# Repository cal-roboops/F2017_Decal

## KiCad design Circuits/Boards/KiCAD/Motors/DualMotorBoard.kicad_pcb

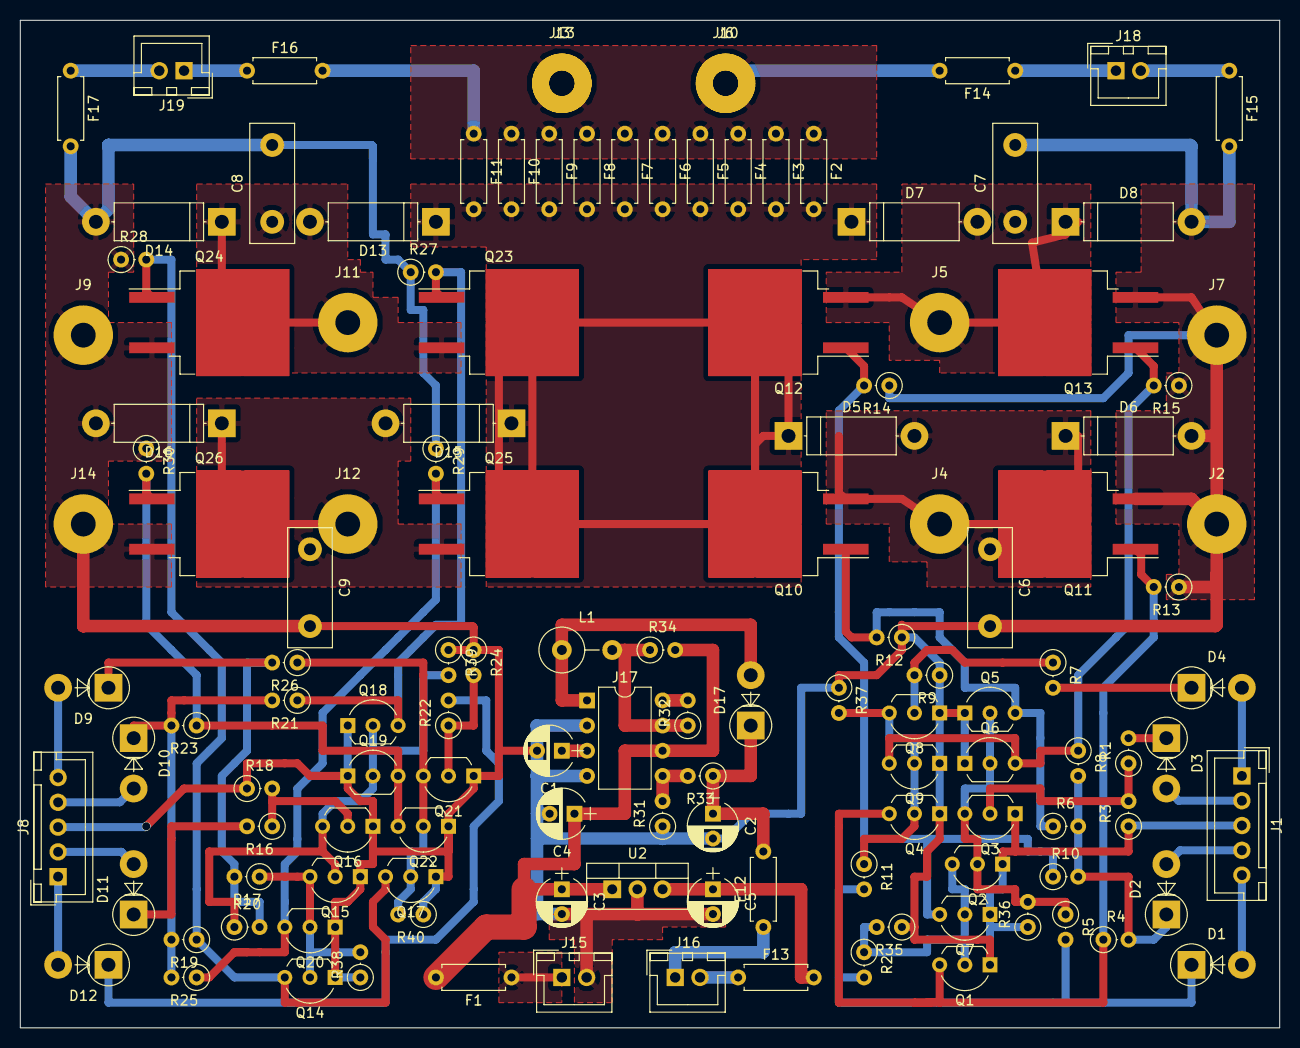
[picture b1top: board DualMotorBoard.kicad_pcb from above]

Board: 2 copper layers, 127.0 x 101.6 mm, 130 parts (0 on the bottom side), 56 nets.

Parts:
C1: 470pF; CP_Radial_D5.0mm_P2.50mm
C2: 470uF; CP_Radial_D5.0mm_P2.50mm
C3: 100uF; CP_Radial_D5.0mm_P2.50mm
C4: 0.33uF; CP_Radial_D5.0mm_P2.50mm
C5: 0.1uF; CP_Radial_D5.0mm_P2.50mm
C6, C7, C8, C9: 1200uF; C_Disc_D12.0mm_W4.4mm_P7.75mm
D1, D2, D3, D4, D9, D10, D11, D12, D17: 1N4007; D_5W_P5.08mm_Vertical_AnodeUp
D5, D6, D7, D8, D13, D14, D15, D16: 1N4007; D_5W_P12.70mm_Horizontal
F1, F2, F3, F4, F5, F6, F7, F8, F9, F10, F11, F12, F13, F14, F15, F16, F17: Polyfuse; R_Axial_DIN0207_L6.3mm_D2.5mm_P7.62mm_Horizontal
J1, J8: Conn_01x05; JST_XH_B05B-XH-A_05x2.50mm_Straight
J2, J3, J4, J5, J6, J7, J9, J10, J11, J12, J13, J14: Conn_01x01; SolderWirePad_single_2-5mmDrill
J15, J16, J18, J19: Conn_01x02; JST_XH_B02B-XH-A_02x2.50mm_Straight
J17: MC34063; DIP-8_W7.62mm
L1: 150uH; L_Axial_L11.0mm_D4.5mm_P5.08mm_Vertical_Fastron_MECC
Q1, Q2, Q3, Q4, Q5, Q6, Q7, Q8, Q9, Q14, Q15, Q16, Q17, Q18, Q19, Q20, Q21, Q22: 2N3904; TO-92_Inline_Wide
Q10, Q11, Q12, Q13, Q23, Q24, Q25, Q26: Q_NMOS_DGS; TO-263-2
R1, R3, R4, R6, R7, R8, R9, R10, R13, R15, R16, R18, R19, R21, R22, R23, R24, R25, R28, R30, R35, R36, R37, R38, R39, R40: 10K; R_Axial_DIN0207_L6.3mm_D2.5mm_P2.54mm_Vertical
R2, R5, R11, R17, R20, R26, R31, R32: 1K; R_Axial_DIN0207_L6.3mm_D2.5mm_P2.54mm_Vertical
R12, R14, R27, R29: 1Meg; R_Axial_DIN0207_L6.3mm_D2.5mm_P2.54mm_Vertical
R33: 20K; R_Axial_DIN0207_L6.3mm_D2.5mm_P2.54mm_Vertical
R34: 0.22; R_Axial_DIN0207_L6.3mm_D2.5mm_P2.54mm_Vertical
U2: LM7805_TO220; TO-220-3_Vertical

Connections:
+BATT: F2.1, F3.1, F4.1, F5.1, F6.1, F7.1, F8.1, F9.1, F10.1, F11.1, F14.2, F16.2, J3.1, J6.1, J10.1, J13.1
/5VUnit/VOUT: C5.1, F13.2, U2.3
/26VUnit/N$5: D17.2, J17.1, L1.1
/26VUnit/N$10: C1.1, J17.3
/26VUnit/N$12: J17.7, L1.2, R32.1, R34.1
/26VUnit/N$13: J17.5, R31.2, R33.2
/26VUnit/VIN: C3.1, C4.1, F1.2, J17.6, R34.2, U2.1
/26VUnit/VOUT: C2.1, D17.1, F12.2, R33.1
/MotorControlUnit_1/BBM: Q1.3, Q4.3, Q11.1, R4.1, R13.2
/MotorControlUnit_1/DVG: D2.1, R4.2, R6.2, R8.2, R10.2
/MotorControlUnit_1/DVSW: D1.1, R2.2, R5.2, R11.2
/MotorControlUnit_1/Dir: D3.1, R1.2
/MotorControlUnit_1/DirSel: Q3.2, R1.1, R3.2
/MotorControlUnit_1/FBM: Q6.3, Q9.3, Q13.1, R8.1, R15.2
/MotorControlUnit_1/MBB: Q1.2, Q2.3, Q7.2, R2.1, R35.2
/MotorControlUnit_1/MBF: Q7.3, Q12.1, R10.1, R14.2
/MotorControlUnit_1/MFB: Q2.2, Q3.3, Q5.2, Q6.2, R5.1, R36.2
/MotorControlUnit_1/MFF: Q5.3, Q10.1, R6.1, R12.2
/MotorControlUnit_1/Speed: D4.1, R7.2
/MotorControlUnit_1/SpeedSel: Q8.2, R7.1, R9.2
/MotorControlUnit_1/VB: C7.1, D7.2, D8.1, J5.1, Q12.3, Q13.2
/MotorControlUnit_1/VF: C6.1, D5.2, D6.1, J4.1, Q10.3, Q11.2
/MotorControlUnit_1/VFUSE: D5.1, D7.1, D13.1, D15.1, F2.2, F3.2, F4.2, F5.2, F6.2, F7.2, F8.2, F9.2, F10.2, F11.2, Q10.2, Q12.2, Q23.2, Q25.2
/MotorControlUnit_1/VG: D2.2, J1.4
/MotorControlUnit_1/VSW: D1.2, J1.5
/MotorControlUnit_1/iSpeed: Q4.2, Q8.3, Q9.2, R11.1, R37.2
/MotorControlUnit_2/BBM: Q14.3, Q17.3, Q24.1, R19.1, R28.2
/MotorControlUnit_2/DVG: D10.1, R19.2, R21.2, R23.2, R25.2
/MotorControlUnit_2/DVSW: D9.1, R17.2, R20.2, R26.2
/MotorControlUnit_2/Dir: D11.1, R16.2
/MotorControlUnit_2/DirSel: Q16.2, R16.1, R18.2
/MotorControlUnit_2/FBM: Q19.3, Q22.3, Q26.1, R23.1, R30.2
/MotorControlUnit_2/MBB: Q14.2, Q15.3, Q20.2, R17.1, R38.2
/MotorControlUnit_2/MBF: Q20.3, Q25.1, R25.1, R29.2
/MotorControlUnit_2/MFB: Q15.2, Q16.3, Q18.2, Q19.2, R20.1, R39.2
/MotorControlUnit_2/MFF: Q18.3, Q23.1, R21.1, R27.2
/MotorControlUnit_2/Speed: D12.1, R22.2
/MotorControlUnit_2/SpeedSel: Q21.2, R22.1, R24.2
/MotorControlUnit_2/VB: C9.1, D15.2, D16.1, J12.1, Q25.3, Q26.2
/MotorControlUnit_2/VF: C8.1, D13.2, D14.1, J11.1, Q23.3, Q24.2
/MotorControlUnit_2/VG: D10.2, J8.4
/MotorControlUnit_2/VSW: D9.2, J8.5
/MotorControlUnit_2/iSpeed: Q17.2, Q21.3, Q22.2, R26.1, R40.2
GND: C1.2, C2.2, C3.2, C4.2, C5.2, C6.2, C7.2, C8.2, C9.2, D6.2, D8.2, D14.2, D16.2, F15.2, F17.2, J1.3, J2.1, J7.1, J8.3, J9.1, J14.1, J15.2, J17.2, J17.4, Q1.1, Q2.1, Q3.1, Q4.1, Q5.1, Q6.1, Q7.1, Q8.1, Q9.1, Q11.3, Q13.3, Q14.1, Q15.1, Q16.1, Q17.1, Q18.1, Q19.1, Q20.1, Q21.1, Q22.1, Q24.3, Q26.3, R3.1, R9.1, R12.1, R13.1, R14.1, R15.1, R18.1, R24.1, R27.1, R28.1, R29.1, R30.1, R31.1, R35.1, R36.1, R37.1, R38.1, R39.1, R40.1, U2.2
unnamed: D3.2, J1.2
unnamed: D4.2, J1.1
unnamed: D11.2, J8.2
unnamed: D12.2, J8.1
unnamed: F1.1, J15.1
unnamed: F12.1, J16.1
unnamed: F13.1, J16.2
unnamed: F14.1, J18.1
unnamed: F15.1, J18.2
unnamed: F16.1, J19.1
unnamed: F17.1, J19.2
unnamed: J17.8, R32.2

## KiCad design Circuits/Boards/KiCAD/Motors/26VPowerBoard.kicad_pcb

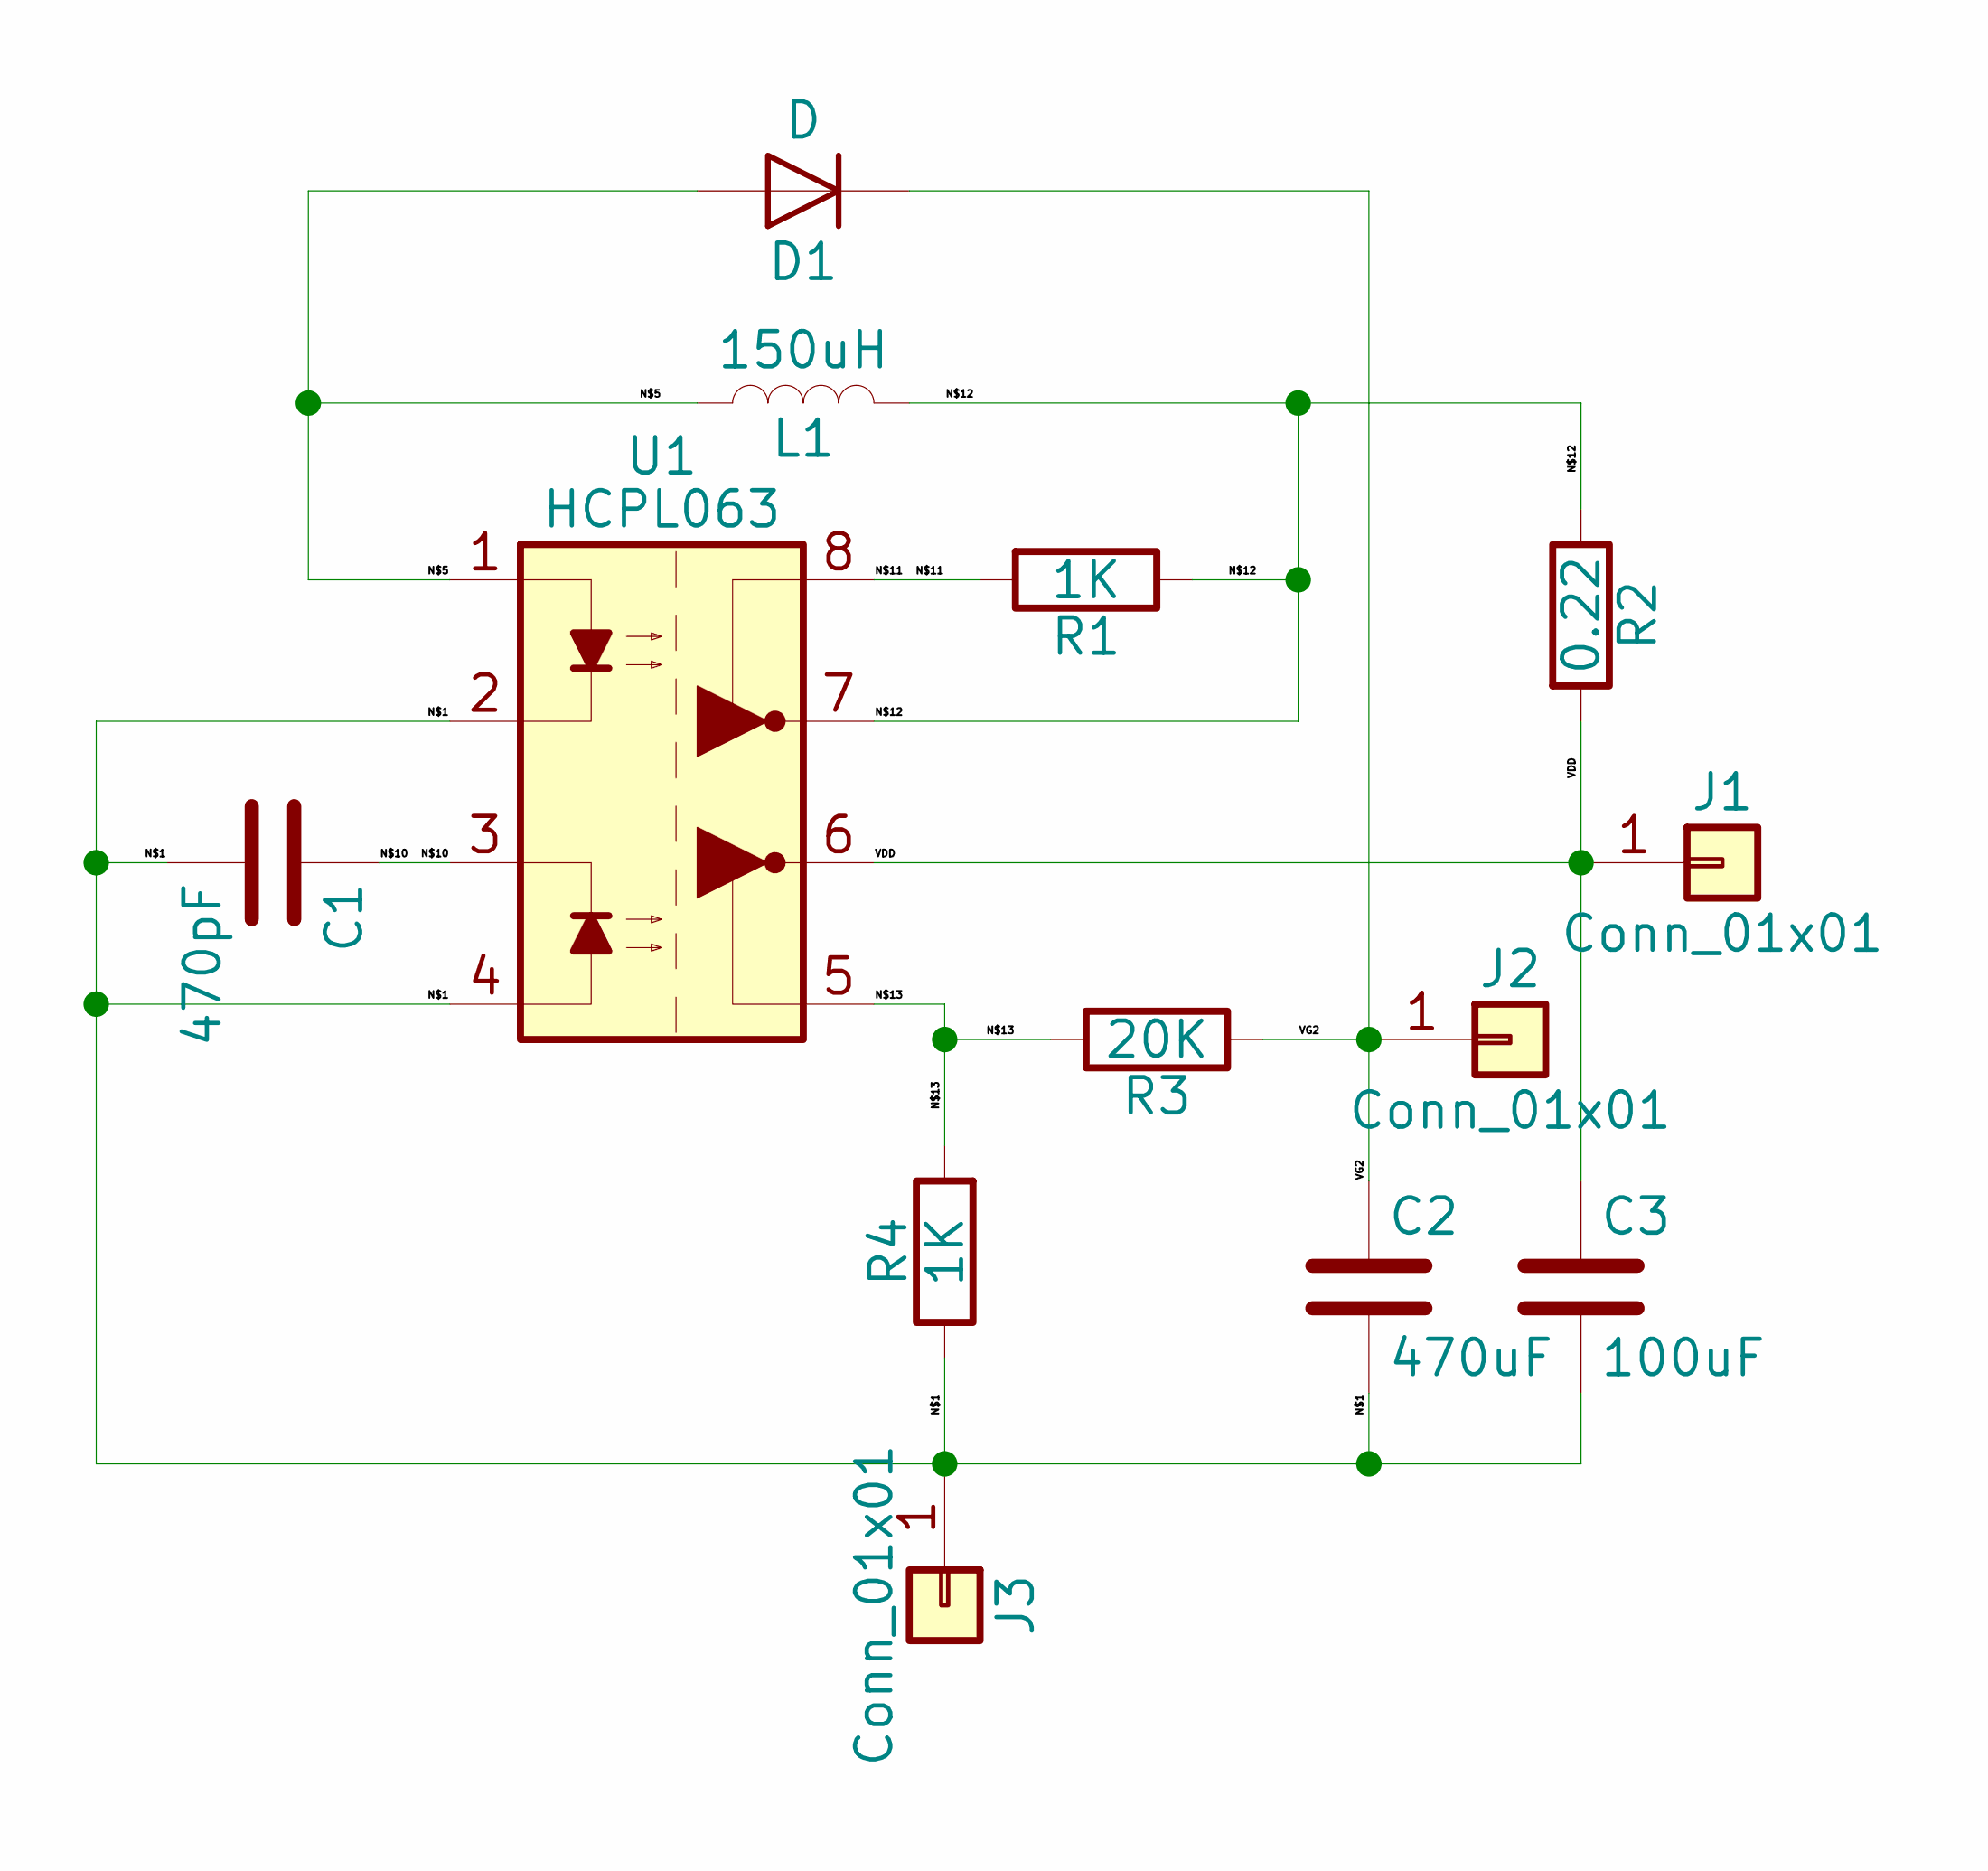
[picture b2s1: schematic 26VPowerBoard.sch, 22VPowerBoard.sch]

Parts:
C1: 470pF; CP_Radial_D5.0mm_P2.50mm
C2: 470uF; CP_Radial_D5.0mm_P2.50mm
C3: 100uF; CP_Radial_D5.0mm_P2.50mm
D1: D; D_5W_P5.08mm_Vertical_AnodeUp
J1, J2: Conn_01x01; MountingHole_2.7mm_Pad_Via
J3: Conn_01x01
L1: 150uH; L_Axial_L11.0mm_D4.5mm_P5.08mm_Vertical_Fastron_MECC
R1, R4: 1K; R_Axial_DIN0207_L6.3mm_D2.5mm_P2.54mm_Vertical
R2: 0.22; R_Axial_DIN0207_L6.3mm_D2.5mm_P2.54mm_Vertical
R3: 20K; R_Axial_DIN0207_L6.3mm_D2.5mm_P2.54mm_Vertical
U1: HCPL063; DIP-8_W7.62mm

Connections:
/N$1: C1.2, C2.2, C3.2, J3.1, R4.1, U1.2 (C1), U1.4 (C2)
/N$5: D1.2 (A), L1.1, U1.1 (A1)
/N$10: C1.1, U1.3 (A2)
/N$11: R1.2, U1.8 (VCC)
/N$12: L1.2, R1.1, R2.1, U1.7 (VO1)
/N$13: R3.2, R4.2, U1.5 (GND)
/VDD: C3.1, J1.1, R2.2, U1.6 (VO2)
/VG2: C2.1, D1.1 (K), J2.1, R3.1

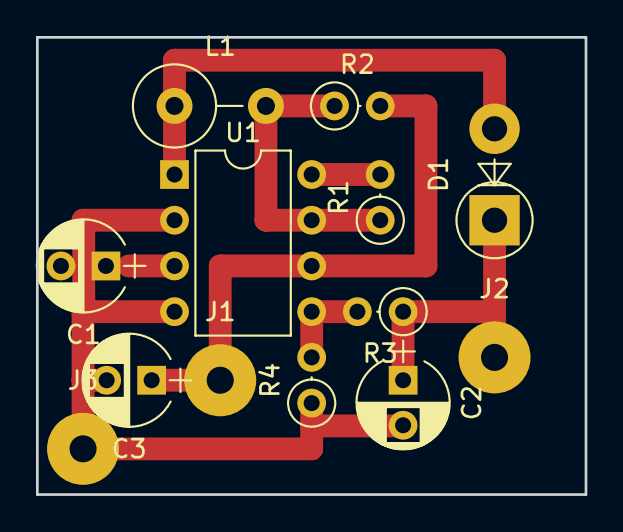
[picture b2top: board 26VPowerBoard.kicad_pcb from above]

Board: 2 copper layers, 30.5 x 25.4 mm, 13 parts (0 on the bottom side), 8 nets.

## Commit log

2017-08-22 Project creation and gitignore added
2017-08-23 added button that prints to debud
2017-08-23 added text box + submit data button for text box
2017-08-24 made client server with text boxes
2017-08-24 Organization and fine tuning of messenger demo
2017-08-28 local webcam button working
2017-09-18 Added backend server, with basic client, and GUI test client
2017-09-18 Updated gitignore and removed qt exe's
2017-09-21 Added Circuit sims
2017-09-21 Making motor controller feedback loop
2017-09-21 Updated Op-Amp in Logic:
2017-09-25 Updated motor simulation
2017-09-25 Ignore simulation raw files
2017-09-26 Save point before PNP control implementation
2017-09-26 Working motor controller simulation
2017-09-27 Small changes
2017-09-27 Pathing Upload
2017-09-28 Split up motor simulation and defiend high pwoer line
2017-09-30 Updated client/server and made changes to motor controller
2017-10-01 server.cpp V4
2017-10-05 Motor controller updates
2017-10-05 Updated motor controller
2017-10-08 Updated server script and vlc multicast
2017-10-08 Updated proxy client and server classes
2017-10-08 ass1
2017-10-08 Setting up rover client
2017-10-15 deleted Circuits, Pathing, and QtMessengerDemo folders
2017-10-15 Simplified motor controller circuit and added FPGA implmentation specifications
2017-10-16 Updated regulator circuits
2017-10-17 json communication/mutexes/function structs
2017-10-17 server now communicates to rover and back to clients
2017-10-18 updated files
2017-10-18 Added custom motor controller tester
2017-10-25 update all clients
2017-10-25 miscellaneous change
2017-10-25 adding assignment3 code - edward
2017-10-25 git example change
2017-10-25 basic impl of topological pathing done
2017-10-26 cleaned up topological pathing code
2017-10-27 changed path drawing
2017-10-27 made window with buttons that change pages
2017-10-27 added regular controls panel
2017-11-01 Fixed motor controller test code - works as expected now
2017-11-01 tank page
2017-11-01 tank done -- can't move to qtproxy yet
2017-11-03 move control_GUI code to QtProxyClient and two ui windows working
2017-11-03 tank done
2017-11-04 Motor control code updated
2017-11-04 Updated gitigore and removed build-Qt dirs
2017-11-06 Updated encoder reading and motor controller
2017-11-08 updated server/client files; added json.hpp
2017-11-08 removed unnecessary line in server.cpp
2017-11-08 added various python scripts for static image processing
2017-11-08 Removed assignment zip
2017-11-08 fixed buffer reset bug
2017-11-10 bug fix to calc_drops function in pathing
2017-11-10 using variance to calc drops
2017-11-10 finished assignemnt 4 and 5
2017-11-10 finished assignment 4 & 5
    :
    "
2017-11-10 implemented slider label
2017-11-11 Updated SSI for encoder and added programmer
2017-11-11 Cleaned up code in programmer to facilitate bug hunt
2017-11-12 updated client.cpp, server.cpp
2017-11-15 added berkeley map
2017-11-15 fixed typo
2017-11-15 Working on programmer and electronics layout
2017-11-17 added 3 buttons to enable/disable buttons (part 1 of assignment 6)
2017-11-17 implemented new buttons to enable/disable control panel
2017-11-17 implemented buttons
2017-11-17 implememnted control buttons
2017-11-21 updated server.cpp
2017-11-29 fix radio button
2017-11-29 cleaned up pathing script and optimized astar
2017-11-29 control panel with serving working. still need to rename files
2017-11-29 one of the json values was wrong
2017-11-30 fixed access control bug
2017-11-30 fixed key press bug
2017-12-01 fixed some more bugs and styled gui more
2017-12-01 more minor style updates
2017-12-01 first attempt at risk function for a pointcloud
2017-12-01 added comments
2017-12-08 small edit
2017-12-21 Adding PCB motor controller board layout
2017-12-21 Fixed gitignore for eagle files
2017-12-22 Finished board files and updated gitignore
2017-12-22 Fixed board CNC errors, ready for cutting on othermill
2017-12-24 Minor updates to Motor Controller
2017-12-24 Updated 22V circuit for bought parts
2017-12-26 Split off 22V & 5V circuits, shrunk motor controller and began adding second to single board
2017-12-27 Single board, two motor update
2017-12-27 Ported Motor Controller to DesignSpark and generated Gerber files for Othermill
2017-12-28 Started moving from EAGLE to KiCAD
2017-12-30 Update KiCAD motor controller and Version 2 simulation
2017-12-31 Fixed KiCAD motor controller
2018-01-05 Rerouted motor controller for smaller size
2018-01-06 Adjusted PCB design
2018-01-07 Created subcircuit for motor control and routing dual controller
2018-01-07 Finished routing dual motor controller, needs to be cleaned up
2018-01-07 Added 26V and 5V units to the Dual motor controller board
2018-01-07 Fixed missing connections and routing
2018-01-07 Added drain resistors to gates
2018-01-16 Fixed gitignore to allow KiCAD pro files
2018-01-16 Motor HF adjustments (gate drain resistors)
2018-01-16 Finished rerouting board with new resistors and caps
2018-01-16 Updated layout errors
2018-01-17 Motor board circuit updated after prototype cut
2018-01-18 Fixed missing connections and routing errors
2018-01-18 Added pin outputs for battery to ground (for external connections)
2018-01-18 Transferred all JXT connections to bottomw traces
2018-01-24 Added Basic Xilinx Echo program for Arty Z7
2018-01-24 Updated echo to test FPGA functionality in addition to ethernet echo
2018-01-26 Fixed synthesis errors in vivado
2018-01-26 Updated gitignores for Xilinx suite
2018-01-27 Started rover client for FPGA
2018-02-08 setup arm stuff, added a widget for controlling camera mask but it has no functionality yet
2018-02-08 setup example code for how to do the arm in main.cpp
2018-02-08 minor variable names changes
2018-02-14 minor changes
2018-02-14 added release file
2018-02-16 Added NRF24L01+ base files and code
2018-02-17 Moved and updated files
2018-02-20 added some more functionality for drawer
2018-02-24 Added testing for nRF24 module
2018-02-24 FPGA controllers added with base for motor, PI, and servo units
2018-02-24 Updated folder structure, added Quartus library folder, and added SSI test module
2018-02-24 Finished SSI reader testing and added samples/sec functionaility
2018-02-25 QTserver
2018-02-26 server working
2018-02-26 server bugs fixed
2018-02-26 Added ready valid interface, clock generator, and base verilog file for rover arm controller
2018-02-27 Working with Zynq
2018-02-27 Updated async fifo and created async uart interface
2018-02-28 Updating Main rover client
2018-02-28 Updating and moving core GUI files
2018-02-28 Overhall of rover client with new json objects and signal driven architecture
2018-02-28 Updated json functionality
2018-03-01 Updated JSON files and gitignore for QT projects
2018-03-02 updated server
2018-03-06 just deleted unnecessary folder
2018-03-06 added proxy arm functionality but haven't set up JSON transmission - waiting on mitch to specifiy JSON values
2018-03-07 Removed QT build dirs from git
2018-03-07 finished setting up additional functionality - mitch needs to enter in new JSON values and transmit them in new functions
2018-03-08 forgot to add a few things... NOW waiting on mitch to transmit new Json values
2018-03-08 Andy's code switched to Edwards Branch
2018-03-08 commited build for Qt
2018-03-10 Removed FPGA Folder to selectively add non auto generated files
2018-03-10 Selectively added FGPA components back in
2018-03-11 Changed to bare metal C++ application
2018-03-11 Updated FPGA CPP application
2018-03-12 JSON linking and touching up on the GUI. Added cleaner signal slot functionality and send features
2018-03-12 Consistency updates for server with signal slot architecture (currently crashes if rover connection is attempted over and over)
2018-03-13 Finalized GUI updates and connected JSON objects. Updating server to refelect Signal Slot architecture found in GUI.
2018-03-13 Fixed server crashing and added more checks to rover connection thread
2018-03-19 data visualizer demo
2018-03-19 Removed all QtMessengerDemo, main application has been split off from this
2018-03-20 Unified frontend GUI and server to reflect some basic JSON feedback & commands
2018-03-20 Fine tuned server feedback for control options, implemented switch statements for easier code expansion to new cases
2018-03-21 Added more feedback and increased verification of actions in server
2018-03-21 3/21
2018-03-26 Added basic data logging functionality/settings
2018-04-10 setup basic ui and wrote comments on other files
2018-04-12 Debugged SSI waveform off 6600 programmer
2018-04-13 Optimized SSI reader for 6600
2018-04-13 forearm at 90 degrees
2018-04-13 Fixed timeout error for AEAT-6600 progmrammer
2018-04-15 Fixed timing and outputs for both reader and programmer (still fails to program)
2018-04-18 Controllable test arm. Importing into main application and pulluing values still need to be done
2018-04-18 Integrated arm graphic into main gui
2018-04-18 Added qml polling for angle values in scene3D
2018-04-18 Fully integrated arm graphic and updated names to reflect ME parts
2018-11-24 fixed an issue in RoverControlServer/roverthread.cpp
